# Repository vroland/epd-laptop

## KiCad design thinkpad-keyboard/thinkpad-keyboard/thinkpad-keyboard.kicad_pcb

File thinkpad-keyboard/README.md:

Keyboard Controller for Thinkpad Keyboards
==========================================

Ever wanted to use an old thinkpad keyboard with an embedded project? This board might be for you!
These keyboards are quite readily available used from ebay and have a nice feel for a laptop keyboard.
This makes them great for embedded projects where you want a keyboard you can *actually* type on.

Compatible Keyboards:

 * Old thinkpad keyboards with a 44 pin connector, like the x60, x61, x220 and probably others.
 
Features
--------

 * Get button press events via SPI
 * Get Trackpoint events via SPI
 * High scan frequency
 * Low power consumption
 * Although the TrackPoint nominally uses 5V, according to my tests the board runs fine on 3.3V.
   This allows to talk directly to a 3.3V-based microcontroller like the ESP32.

Getting Started
---------------

Although the firmware is based on the arduino firmware, the Atmega32 does not usually come with the Arduino bootloader flashed.
Thus, you need an AVR ISP-Compatible programmer.

1. Prerequisites: Install platformio
2. Compile the firmware: `pio run -t build`
3. Burn the fuses to use the external oscillator: `pio run -t fuses`
4. Upload: `pio run -t upload`
5. Enjoy!

Future
------

 * Currently, the 40-pin connector of the keyboard is broken out on the PCB, mainly for debug puropses.
   For a second revision, this would not be needed.
 
FAQ
---

* Q: Where do I get the receptable for this strange connector?
  A: The AA01B-S040VA1 is available on AliExpress.

References
----------

* https://www.instructables.com/id/Make-a-ThinkPad-keyboard-USB-adapter-with-Arduino/
* https://github.com/rampadc/arduino-trackpoint-extended
* https://hackaday.com/2018/12/04/teensy-liberates-the-thinkpad-keyboard/
* https://larsee.com/blog/2018/06/thinkpad-usb-keyboard-adapter/

Licenses
--------

Case drawings, the keyboard pcband schematic are licensed under a  <a rel="license" href="http://creativecommons.org/licenses/by/4.0/">Creative Commons Attribution 4.0 International License</a>.

Firmware and utilities are licensed unter the terms of the MIT license.

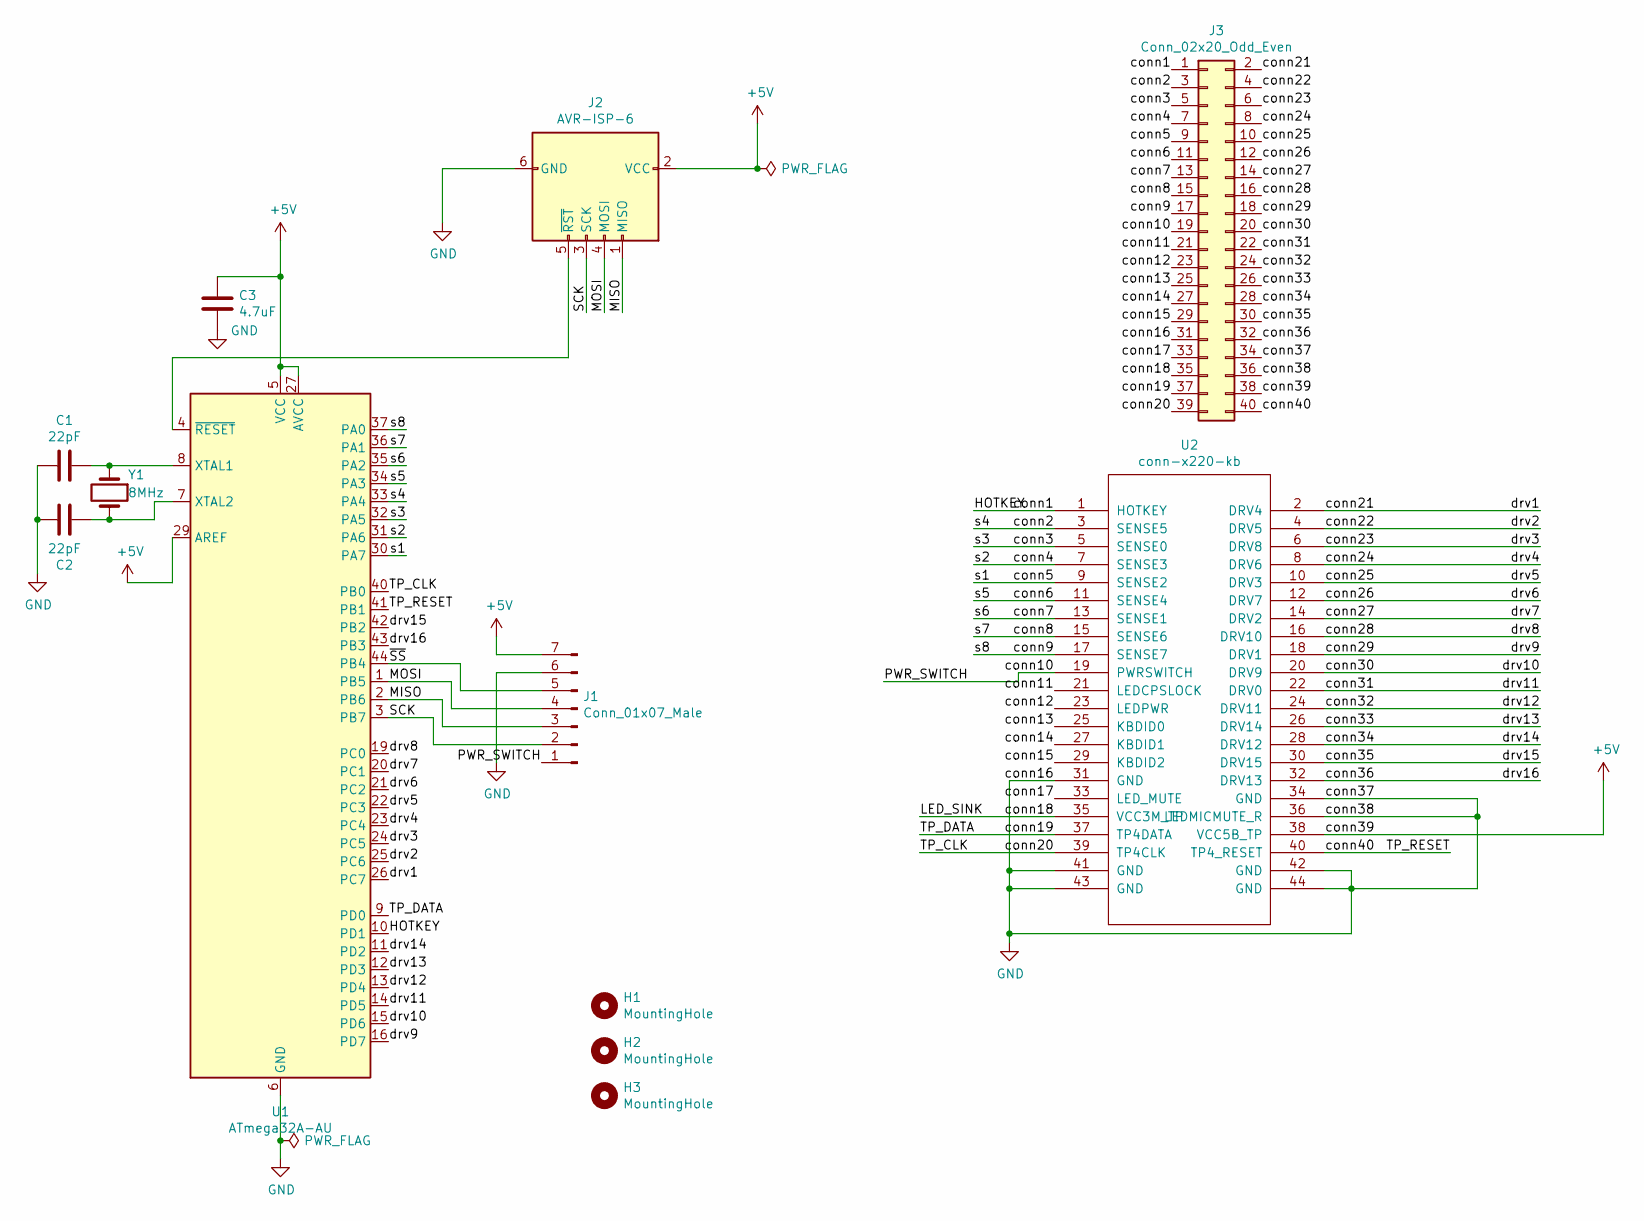
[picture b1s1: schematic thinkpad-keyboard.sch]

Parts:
C1, C2: 22pF; C_0603_1608Metric
C3: 4.7uF; C_0603_1608Metric
H1, H2, H3: MountingHole; MountingHole_2.2mm_M2
J1: Conn_01x07_Male; PinHeader_1x07_P2.54mm_Vertical
J2: AVR-ISP-6; PinHeader_2x03_P2.54mm_Vertical
J3: Conn_02x20_Odd_Even; PinHeader_2x20_P2.54mm_Vertical
U1: ATmega32A-AU; TQFP-44_10x10mm_P0.8mm
U2: conn-x220-kb; AA01B-S040VA1
Y1: 8MHz; Crystal_SMD_5032-2Pin_5.0x3.2mm

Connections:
+5V: C3.2, J1.7, J2.2 (VCC), J3.38, U1.5 (VCC), U1.17 (VCC), U1.27 (AVCC), U1.29 (AREF), U1.38 (VCC), U2.38 (VCC5B_TP)
/HOTKEY: J3.1, U1.10 (PD1), U2.1 (HOTKEY)
/LED_SINK: J3.35, U2.35 (VCC3M_TP)
/MISO: J1.3, J2.1 (MISO), U1.2 (PB6)
/MOSI: J1.4, J2.4 (MOSI), U1.1 (PB5)
/PWR_SWITCH: J1.1, J3.19, U2.19 (PWRSWITCH)
/SCK: J1.2, J2.3 (SCK), U1.3 (PB7)
/TP_CLK: J3.39, U1.40 (PB0), U2.39 (TP4CLK)
/TP_DATA: J3.37, U1.9 (PD0), U2.37 (TP4DATA)
/TP_RESET: J3.40, U1.41 (PB1), U2.40 (TP4_RESET)
/conn2: J3.3, U1.33 (PA4), U2.3 (SENSE5)
/conn3: J3.5, U1.32 (PA5), U2.5 (SENSE0)
/conn4: J3.7, U1.31 (PA6), U2.7 (SENSE3)
/conn5: J3.9, U1.30 (PA7), U2.9 (SENSE2)
/conn6: J3.11, U1.34 (PA3), U2.11 (SENSE4)
/conn7: J3.13, U1.35 (PA2), U2.13 (SENSE1)
/conn8: J3.15, U1.36 (PA1), U2.15 (SENSE6)
/conn9: J3.17, U1.37 (PA0), U2.17 (SENSE7)
/conn11: J3.21, U2.21 (LEDCPSLOCK)
/conn12: J3.23, U2.23 (LEDPWR)
/conn13: J3.25, U2.25 (KBDID0)
/conn14: J3.27, U2.27 (KBDID1)
/conn15: J3.29, U2.29 (KBDID2)
/conn17: J3.33, U2.33 (LED_MUTE)
/conn21: J3.2, U1.26 (PC7), U2.2 (DRV4)
/conn22: J3.4, U1.25 (PC6), U2.4 (DRV5)
/conn23: J3.6, U1.24 (PC5), U2.6 (DRV8)
/conn24: J3.8, U1.23 (PC4), U2.8 (DRV6)
/conn25: J3.10, U1.22 (PC3), U2.10 (DRV3)
/conn26: J3.12, U1.21 (PC2), U2.12 (DRV7)
/conn27: J3.14, U1.20 (PC1), U2.14 (DRV2)
/conn28: J3.16, U1.19 (PC0), U2.16 (DRV10)
/conn29: J3.18, U1.16 (PD7), U2.18 (DRV1)
/conn30: J3.20, U1.15 (PD6), U2.20 (DRV9)
/conn31: J3.22, U1.14 (PD5), U2.22 (DRV0)
/conn32: J3.24, U1.13 (PD4), U2.24 (DRV11)
/conn33: J3.26, U1.12 (PD3), U2.26 (DRV14)
/conn34: J3.28, U1.11 (PD2), U2.28 (DRV12)
/conn35: J3.30, U1.42 (PB2), U2.30 (DRV15)
/conn36: J3.32, U1.43 (PB3), U2.32 (DRV13)
/~SS: J1.5, U1.44 (PB4)
GND: C1.2, C2.1, C3.1, J1.6, J2.6 (GND), J3.31, J3.34, J3.36, U1.6 (GND), U1.18 (GND), U1.28 (GND), U1.39 (GND), U2.31 (GND), U2.34 (GND), U2.36 (LEDMICMUTE_R), U2.41 (GND), U2.42 (GND), U2.43 (GND), U2.44 (GND)
unnamed: C1.1, U1.8 (XTAL1), Y1.1
unnamed: C2.2, U1.7 (XTAL2), Y1.2
unnamed: J2.5 (~RST), U1.4 (~RESET)

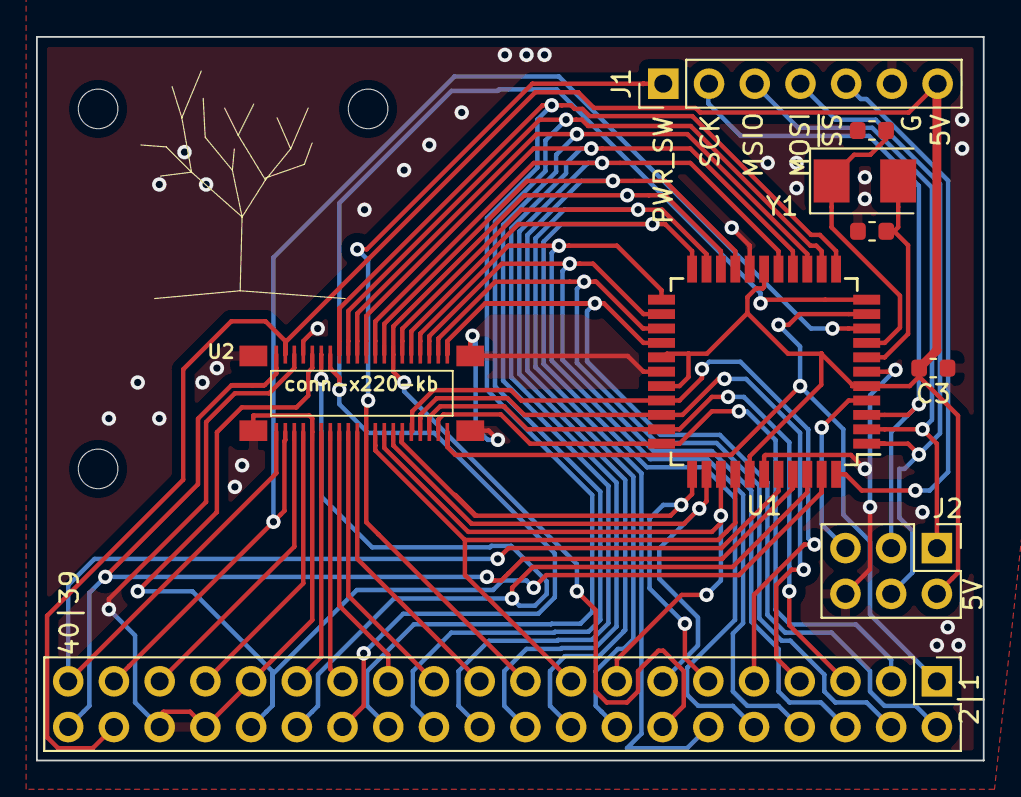
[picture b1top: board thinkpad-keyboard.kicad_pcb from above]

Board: 2 copper layers, 52.6 x 40.2 mm, 12 parts (0 on the bottom side), 45 nets.

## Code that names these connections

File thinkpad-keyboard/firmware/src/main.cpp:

#include <Arduino.h>
#include <stdint.h>
#include <SPI.h>
#include <math.h>
#include "TrackPoint.h"

#include "keys.h"

#define NUM_DRIVE 16

static uint8_t keystate[16] = {0, 0, 0, 0, 0, 0, 0, 0,
                               0, 0, 0, 0, 0, 0, 0, 0};

const int DRIVE_PINS[NUM_DRIVE] = {23, 22, 21, 20, 19, 18, 17, 16, 15, 14, 13, 12, 11, 10, 3, 2};

#define TP_CLOCK 0
#define TP_RESET 1
#define TP_DATA 8

#define HOTKEY 9

TrackPoint trackpoint(TP_CLOCK, TP_DATA, TP_RESET, true);

uint8_t scan(void);

void spi_send(uint8_t* buf, int length) {
    SPI.beginTransaction(SPISettings(8000000, MSBFIRST, SPI_MODE3));
    digitalWrite(SS, LOW); // enable Slave Select
    // send test string
    for (int i=0; i < length; i++)
    {
      SPI.transfer (buf[i]);
    }
    digitalWrite(SS, HIGH); // disable Slave Select
    SPI.endTransaction();
}

volatile static TPEvent report;
volatile static int report_new = 0;

ISR(USART_RXC_vect)
{
    static TrackPoint::DataReport wip_report = {
        .state = 0b00001000,
        .x = 0,
        .y = 0,
    };
    static uint8_t bytes_received = 0;
    ((uint8_t*)&wip_report)[bytes_received++] = UDR;

    if (bytes_received == sizeof(wip_report)) {
        *((uint8_t*)&report.state) = wip_report.state;
        report.x = wip_report.x;
        report.y = wip_report.y;
        bytes_received = 0;
        report_new = 1;
    }
}

void setup (void) {
    digitalWrite(SS, HIGH); // disable Slave Select
    SPI.begin ();
    DDRA = 0x0; // Port A as input
    PORTA = 0xFF; // Activate Pull-Up

    for (int i=0; i < NUM_DRIVE; i++) {
        pinMode(DRIVE_PINS[i], INPUT);
    }

    pinMode(HOTKEY, INPUT_PULLUP);

    trackpoint.reset();
	trackpoint.setSensitivityFactor(0xC0);
	trackpoint.setStreamMode();

    // Clock must be INPUT to enable USART slave mode
    pinMode(TP_CLOCK, INPUT);

    // Enable synchronous serial
    UCSRB = (1<<RXEN) | (1<<RXCIE);

    // Synchronous mode, odd parity, 8 data, 1 stop bit
    UCSRC = (1<<URSEL) | (1<<UMSEL) | (1<<UPM1) | (1<<UPM0) |  (1<<UCSZ1) | (1<<UCSZ0);
}

inline uint8_t scan_line(int l) {
    pinMode(DRIVE_PINS[l], OUTPUT);
    digitalWrite(DRIVE_PINS[l], LOW);
    uint8_t value = PINA;
    pinMode(DRIVE_PINS[l], INPUT);
    return value;
}

uint8_t scan() {
    uint8_t event = 0xFF;
    for (int line = 0; line < NUM_DRIVE; line++) {
        uint8_t result = scan_line(line);
        uint8_t newly_active = (~keystate[line]) & (~result);
        uint8_t newly_inactive = keystate[line] & result;

        if (newly_inactive) {
            // more than one key set / unset at a time (newly_active is not a
            // power of 2 or 0) is considered ghosting
            if ((newly_inactive & (newly_inactive - 1)) == 0) {
                if (event == 0xFF) {
                    keystate[line] ^= newly_inactive;
                    event = (line * 8 + (sizeof(unsigned int) * 8 - __builtin_clz((unsigned int)newly_inactive) - 1));
                } else {
                    // ghosting occured
                    event = 0xFF;
                    break;
                }
            };
        }

        if (newly_active) {
            // more than one key set / unset at a time (newly_active is not a
            // power of 2 or 0) is considered ghosting
            if ((newly_active & (newly_active - 1)) == 0) {
                if (event == 0xFF) {
                    keystate[line] ^= newly_active;
                    event = (line * 8 + (sizeof(unsigned int) * 8 - __builtin_clz((unsigned int)newly_active) - 1)) | 0x80;
                } else {
                    // ghosting occured
                    event = 0xFF;
                    break;
                }
            };
        }
    }
    if (event != 0xFF) {
        return event;
    // query HOTKEY
    } else {
        uint8_t pressed = !digitalRead(HOTKEY);
        static int hotkey_state = 0;
        if (pressed && !hotkey_state) {
            event = 126 | 0x80;
            hotkey_state = 1;
        } else if (!pressed && hotkey_state) {
            event = 126;
            hotkey_state = 0;
        }
    }
    return event;
}

void loop (void) {
    uint8_t event = scan();

    if (report_new) {
        uint8_t buf[4];
        buf[0] = EventKind::TRACKPOINT_EVENT;
        memcpy(buf + 1, &report, 3);
        spi_send(buf, sizeof(buf));
        report_new = 0;
    }

    if (event != 0xFF) {
        uint8_t buf[2] = {EventKind::KEYBOARD_EVENT, event};
        spi_send(buf, sizeof(buf));
    }
}

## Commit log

2020-09-08 add keyboard readme
2020-09-08 add instructions
2020-10-15 add fuel gauge device overlay
